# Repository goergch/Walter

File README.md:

# Walter
Walter is a self-made, dangerous, industrial robot with 6 DOF. Right in the middle of development. Check the [Documentation](http://walter.readthedocs.io). Contact me via the [hackaday page](https://hackaday.io/post/53678).

### Contents
    /cad 	    CAD designs (TurboCAD)
    /theory     mainly kinematics
    /code       code of Cortex, Trajectory Planner, and Webserver  
    /schematics schematics of Cortex and its power board
    /docs		source of Walter's [Documentation](https://http://walter.readthedocs.io)
    /datasheets datasheets of components Walter is made of

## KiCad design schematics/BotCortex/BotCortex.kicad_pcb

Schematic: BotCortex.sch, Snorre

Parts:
1.2K1, 1.2K2, 1.2k1, 1.2k2: R; R4
C1: 47uF; C_Radial_D8_L13_P3.8
C2, C6, C12, C14, C16: 100nF; C_Disc_D3_P2.5
C3: 220uF; C_Radial_D5_L6_P2.5
C4, C5: 10uF; C_Radial_D5_L6_P2.5
C7: 47uF; C_Radial_D5_L6_P2.5
C11: 2200uF; C_Radial_D7.5_L11.2_P2.5
C13: 1000uF; C_Radial_D7.5_L11.2_P2.5
D1, D10: Diode; Diode_DO-35_SOD27_Horizontal_RM10
D5: 1N5822; Diode_DO-35_SOD27_Horizontal_RM10
F1: FUSE; FUSE_HOLDER
P1: 2x Serial; Socket_MOLEX-KK-RM2-54mm_Lock_5pin_straight
P2: Herkulex Servo; Molex_KK_6410-04
P3: Encoder Socket 1; Molex_KK_6410-04
P4: Encoder Socket 0; Molex_KK_6410-04
P5: Stepper Elbow; Molex_KK_6410-04
P6: Power In uC Servo 9V; bornier3
P7: Power Out uC Servo; Molex_KK_6410-03
P8: Stepper Forearm; Molex_KK_6410-04
P9: Stepper Wrist; Molex_KK_6410-04
P10: Stepper Upperarm; Molex_KK_6410-04
P11: Stepper Hip; Molex_KK_6410-04
P12: POWER_IN; bornier4
P13: PowerEnableIn; Molex_KK_6410-02
P14: Power Stepper 2; bornier2
P15: Power Stepper 3; bornier2
P16: Power Stepper 4; bornier2
P17: PowerEnableOut; Molex_KK_6410-02
P18: Power Stepper 5; bornier2
P19: Thermal Printer 5V; bornier2
P20: POTI 10K; Molex_KK_6410-03
P21: Reset_Conn; 1pin
P22: Reset Conn; 1pin
P23: LED-Driver-I2C; Molex_KK_6410-04
P24: UART6; PINHEAD1-2
P25: Thermal_Printer; Molex_KK_6410-04
P26: Reset Anschluss; Molex_KK_6410-03
P28: Power Stepper 1; bornier2
Q1, Q2: BC237; TO-92_Molded_Wide
R1: 220; R4
R5, R6: 120; R4
R8, R10: 1K; R4
REL1, REL2: Relay_1xON; RELAIS_HF115F
SW2: reset; SW_PUSH-12mm
U1: 7805; 78XX-TO-220
U2, U3: LM7809ACT; TO-220
U4: Teensy_3.5

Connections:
/3.3V: 1.2K1.1, 1.2K2.1, 1.2k1.1, 1.2k2.1, C16.1, P20.1, P25.4, U4.46 (3.3V_(250mA))
/5V: P12.3, P19.1
/12V: D5.2 (A), P12.2
/24V: F1.1, P12.1
/+5V: C7.1, P3.4, P4.4, P23.1, U1.VO, U4.48 (Vin_(3.3/5V))
/CLK0: P11.2, U4.6 (4/SDA2/PWM)
/CLK1: P10.2, U4.9 (7/SCL0/MOSI0/RX3/PWM)
/CLK2: P8.2, U4.12 (10/TX2/PWM)
/CLK3: P5.2, U4.17 (25)
/CLK4: P9.2, U4.20 (28/MOSI0)
/DIR0: P11.3, U4.7 (5/MISO1/TX1/PWM)
/DIR1: P10.3, U4.10 (8/SDA0/MISO0/TX3/PWM)
/DIR2: P8.3, U4.13 (11/MOSI0)
/DIR3: P5.3, U4.18 (26/SCL2/TX1)
/DIR4: P9.3, U4.21 (29/PWM)
/EN1: P10.4, U4.11 (9/RX2/PWM)
/EN2: P8.4, U4.14 (12/MISO0)
/EN3: P5.4, U4.19 (27/SCK0/RC1)
/EN4: P9.4, U4.22 (30/PWM)
/En0: P11.4, U4.8 (6/PWM)
/LoggerTX: P1.5, U4.24 (32/SCK1/TX4/A13)
/PowerOnServo: P17.2, R10.2
/PowerOnStepper: P17.1, R8.2
/PowerSupplyServo: P13.1, U4.44 (22/A8/PWM)
/PowerSupplyStepper: P13.2, U4.45 (23/A9/PWM)
/RESET: P21.1, P26.2, SW2.2
/RX5: P1.2, U4.26 (34/A15/SDA0/RX5)
/RX6: P24.2, P25.2
/Reset-LED: P26.3, R1.2
/SCl0: 1.2k1.2, P4.3, U4.41 (19/A5/SCL0)
/SCl1: 1.2K2.2, P3.3, P23.3, U4.29 (37/A18/PWM/SCL1)
/SDA0: 1.2k2.2, P4.2, U4.40 (18/A4/SDA0)
/SDA1: 1.2K1.2, P3.2, P23.2, U4.30 (38/A19/PWM/SDA1)
/TX5: P1.3, U4.25 (33/A14SCL0TX5)
/TX6: P24.1, P25.3
/VDDServo9V: P2.2, P6.3
/VDD_Servo_9V: P7.3, REL1.4
/VDD_uC_5V: C1.1, C2.1, C3.1, C6.1, P6.2, P7.2, U1.VI, U2.3 (OUT)
GNDPWR: C1.2, C2.2, C3.2, C6.2, C7.2, C11.2, C12.2, C13.2, C14.2, C16.2, P1.1, P2.1, P3.1, P4.1, P5.1, P6.1, P7.1, P8.1, P9.1, P10.1, P11.1, P12.4, P14.2, P15.2, P16.2, P18.2, P19.2, P20.3, P23.4, P25.1, P26.1, P28.2, Q1.3 (E), Q2.3 (E), SW2.1, U1.GND, U2.2 (GND), U3.2 (GND), U4.1 (GND), U4.34 (GND)
unnamed: C4.2, D10.1 (K), R5.1, REL2.2
unnamed: C5.2, D1.1 (K), R6.1, REL1.2
unnamed: C4.1, C5.1, C11.1, C12.1, D5.1 (K), R5.2, R6.2, U2.1 (IN), U3.1 (IN)
unnamed: C13.1, C14.1, REL1.3, U3.3 (OUT)
unnamed: D1.2 (A), Q1.1 (C), REL1.1
unnamed: D10.2 (A), Q2.1 (C), REL2.1
unnamed: F1.2, REL2.3
unnamed: P2.3, U4.2 (0/MOSI1/RX1)
unnamed: P2.4, U4.3 (1/MISO1/TX1)
unnamed: P14.1, P15.1, P16.1, P18.1, P28.1, REL2.4
unnamed: P20.2, U4.37 (15/A1)
unnamed: P22.1, U4.49 (Reset)
unnamed: Q1.2 (B), R8.1
unnamed: Q2.2 (B), R10.1
unnamed: R1.1, U4.27 (35/A16/PWM)

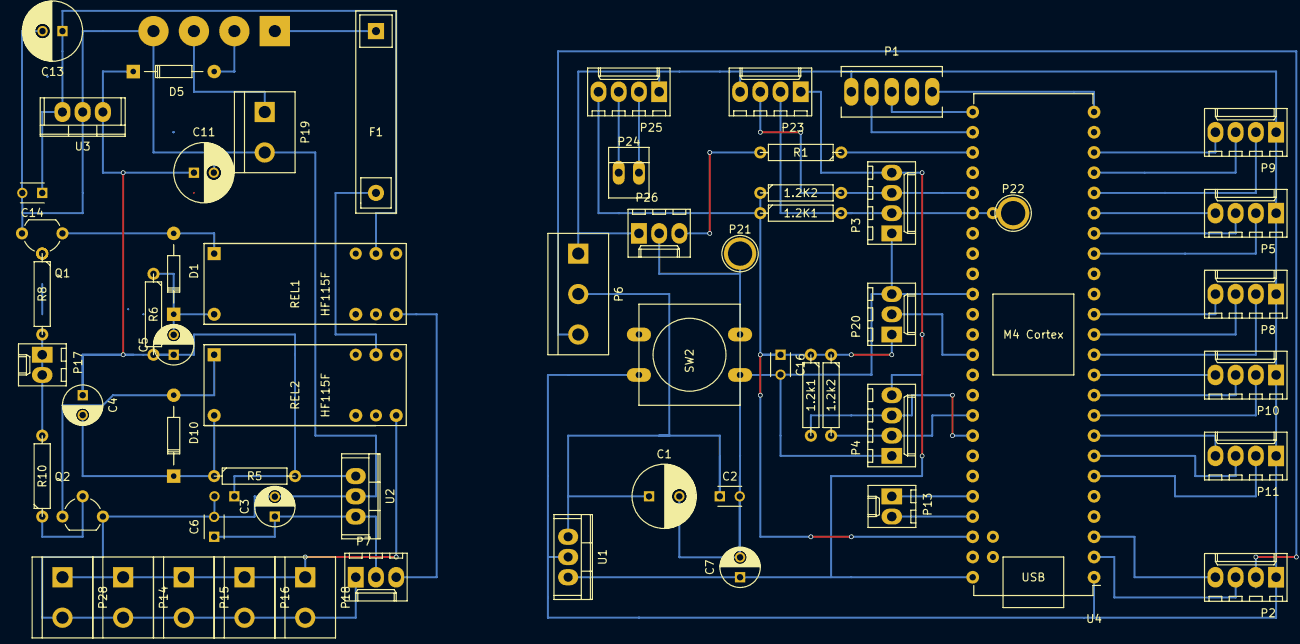
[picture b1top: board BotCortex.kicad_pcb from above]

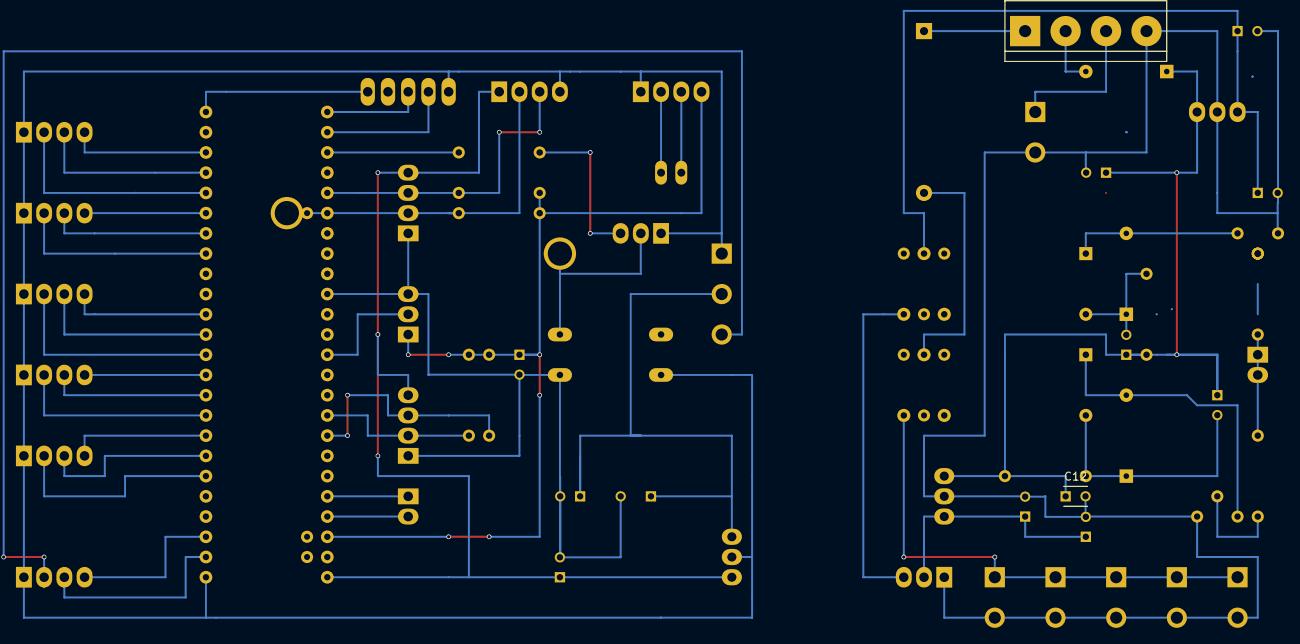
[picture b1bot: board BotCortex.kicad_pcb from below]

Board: 2 copper layers, 61 parts (2 on the bottom side), 54 nets.

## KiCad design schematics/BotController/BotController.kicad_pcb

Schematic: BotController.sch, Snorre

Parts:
AVR1: AVR-ISP-6
C1: 100uF; C_Radial_D8_L13_P3.8
C2, C6, C12, C14, C15, C16: 100nF; C_Disc_D3_P2.5
C3: 220uF; C_Radial_D5_L6_P2.5
C4, C5: 10uF; C_Radial_D5_L6_P2.5
C7: 100uF; C_Radial_D5_L6_P2.5
C11: 2200uF; C_Radial_D7.5_L11.2_P2.5
C13: 1000uF; C_Radial_D7.5_L11.2_P2.5
D1, D10: Diode; Diode_DO-35_SOD27_Horizontal_RM10
D2: LED; LED-3MM
D4: D; Diode_DO-35_SOD27_Horizontal_RM10
D5: 1N5822; Diode_DO-35_SOD27_Horizontal_RM10
F1: FUSE; FUSE_HOLDER
IC1: ATMEGA644A-P; DIP-40_W15.24mm
P1: 2x Serial; Socket_MOLEX-KK-RM2-54mm_Lock_5pin_straight
P2: Herkulex Servo; Molex_KK_6410-04
P3: Encoder Socket 0; Molex_KK_6410-04
P4: Encoder Socket; Molex_KK_6410-04
P5: Stepper 1 WristTurn; Molex_KK_6410-04
P6: Power In uC Servo; bornier3
P7: Power Out uC Servo; Molex_KK_6410-03
P8: Stepper Forearm; Molex_KK_6410-04
P9: Stepper Upperarm; Molex_KK_6410-04
P10: Stepper Shoulder; Molex_KK_6410-04
P11: Stepper Hip; Molex_KK_6410-04
P12: POWER_IN; bornier4
P13: PowerEnableIn; Molex_KK_6410-02
P14: Power Stepper 2; bornier2
P15: Power Stepper 3; bornier2
P16: Power Stepper 4; bornier2
P17: PowerEnableOut; Molex_KK_6410-02
P18: Power Stepper 5; bornier2
P19: ODroid Power; bornier2
P20: POTI 10K; Molex_KK_6410-03
P28: Power Stepper 1; bornier2
Q1, Q2: BC237; TO-92_Molded_Wide
R1: 10K; R4
R2, R8, R10: 1K; R4
R3: 4.7K; R4(8)
R4: 4.7K; R4(7)
R5, R6: 120; R4
REL1, REL2: Relay_1xON; RELAIS_HF115F
SW2: reset; SW_PUSH-12mm
U1: 7805; 78XX-TO-220
U2, U3: LM7809ACT; TO-220
X1: QUARZ_OSSCILATOR; OSC_DIP14

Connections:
/5V: P12.3, P19.1
/12V: D5.2 (A), P12.2
/24V: F1.1, P12.1
/+5V: AVR1.2, C7.1, C16.1, D4.1 (K), IC1.10 (VCC), IC1.30 (AVCC), IC1.32 (AREF), P4.4, P20.1, R1.1, R3.1, R4.1, U1.VO, X1.14
/CLK1: IC1.37 ((PCINT3/ADC3)PA3), P5.2
/CLK2: IC1.34 ((PCINT6/ADC6)PA6), P8.2
/CLK3: IC1.28 ((PCINT22/TOSC1)PC6), P9.2
/CLK4: IC1.25 ((PCINT19/TMS)PC3), P10.2
/CLK5: IC1.20 ((PCINT30/OC2B/ICP)PD6), P11.2
/ConflictEncoderGND: IC1.1 ((PCINT8/T0/XCK)PB0), P3.1
/ConflictEncoderVDD: IC1.2 ((PCINT9/CLKO/T1)PB1), P3.4
/DIR1: IC1.38 ((PCINT2/ADC2)PA2), P5.3
/DIR2: IC1.35 ((PCINT5/ADC5)PA5), P8.3
/DIR3: IC1.29 ((PCINT23/TOSC2)PC7), P9.3
/DIR4: IC1.26 ((PCINT20/TDO)PC4), P10.3
/DIR5: IC1.21 ((PCINT31/OC2A)PD7), P11.3
/EN1: IC1.39 ((PCINT1/ADC1)PA1), P5.4
/EN2: IC1.36 ((PCINT4/ADC4)PA4), P8.4
/EN3: IC1.33 ((PCINT7/ADC7)PA7), P9.4
/EN4: IC1.27 ((PCINT21/TDI)PC5), P10.4
/En5: IC1.24 ((PCINT18/TCK)PC2), P11.4
/LoggerTX: IC1.18 ((PCINT28/XCK1/OC1B)PD4), P1.5
/MISO: AVR1.1, IC1.7 ((PCINT14/MISO)PB6)
/MOSI: AVR1.4, IC1.6 ((PCINT13/MOSI)PB5)
/PowerOnServo: P17.2, R10.2
/PowerOnStepper: P17.1, R8.2
/PowerSupplyServo: IC1.4 ((PCINT11/AIN1/OC0)PB3), P13.1
/PowerSupplyStepper: IC1.5 ((PCINT12/OC0B/~SS~)PB4), P13.2
/RST: AVR1.5, C15.1, D4.2 (A), IC1.9 (~RESET), R1.2, SW2.2
/RXD0: IC1.14 ((PCINT24/RXD0)PD0), P1.2
/RXD1: IC1.16 ((PCINT26/RXD1/INT0)PD2), P2.3
/SCK: AVR1.3, IC1.8 ((PCINT15/SCK)PB7)
/SCl: IC1.22 ((PCINT16/SCL)PC0), P3.3, P4.3, R3.2
/SDA: IC1.23 ((PCINT17/SDA)PC1), P3.2, P4.2, R4.2
/TAL: IC1.13 (XTAL1), X1.8
/TXD0: IC1.15 ((PCINT25/TXD0)PD1), P1.3
/TXD1: IC1.17 ((PCINT27/TXD1/INT1)PD3), P2.4
/VDDServo: P2.2, P6.3
/VDD_Servo: P7.3, REL1.4
/VDD_uC: C3.1, C6.1, P7.2, U2.3 (OUT)
/VDDuC: C1.1, C2.1, P6.2, U1.VI
GNDPWR: AVR1.6, C1.2, C2.2, C3.2, C6.2, C7.2, C11.2, C12.2, C13.2, C14.2, C15.2, C16.2, D2.1 (K), IC1.11 (GND), IC1.31 (GND), P1.1, P1.4, P2.1, P4.1, P5.1, P6.1, P7.1, P8.1, P9.1, P10.1, P11.1, P12.4, P14.2, P15.2, P16.2, P18.2, P19.2, P20.3, P28.2, Q1.3 (E), Q2.3 (E), SW2.1, U1.GND, U2.2 (GND), U3.2 (GND), X1.7
unnamed: C4.2, D10.1 (K), R5.1, REL2.2
unnamed: C5.2, D1.1 (K), R6.1, REL1.2
unnamed: C4.1, C5.1, C11.1, C12.1, D5.1 (K), R5.2, R6.2, U2.1 (IN), U3.1 (IN)
unnamed: C13.1, C14.1, REL1.3, U3.3 (OUT)
unnamed: D1.2 (A), Q1.1 (C), REL1.1
unnamed: D2.2 (A), R2.1
unnamed: D10.2 (A), Q2.1 (C), REL2.1
unnamed: F1.2, REL2.3
unnamed: IC1.3 ((PCINT10/AIN0/INT2)PB2), R2.2
unnamed: IC1.40 ((PCINT0/ADC0)PA0), P20.2
unnamed: P14.1, P15.1, P16.1, P18.1, P28.1, REL2.4
unnamed: Q1.2 (B), R8.1
unnamed: Q2.2 (B), R10.1

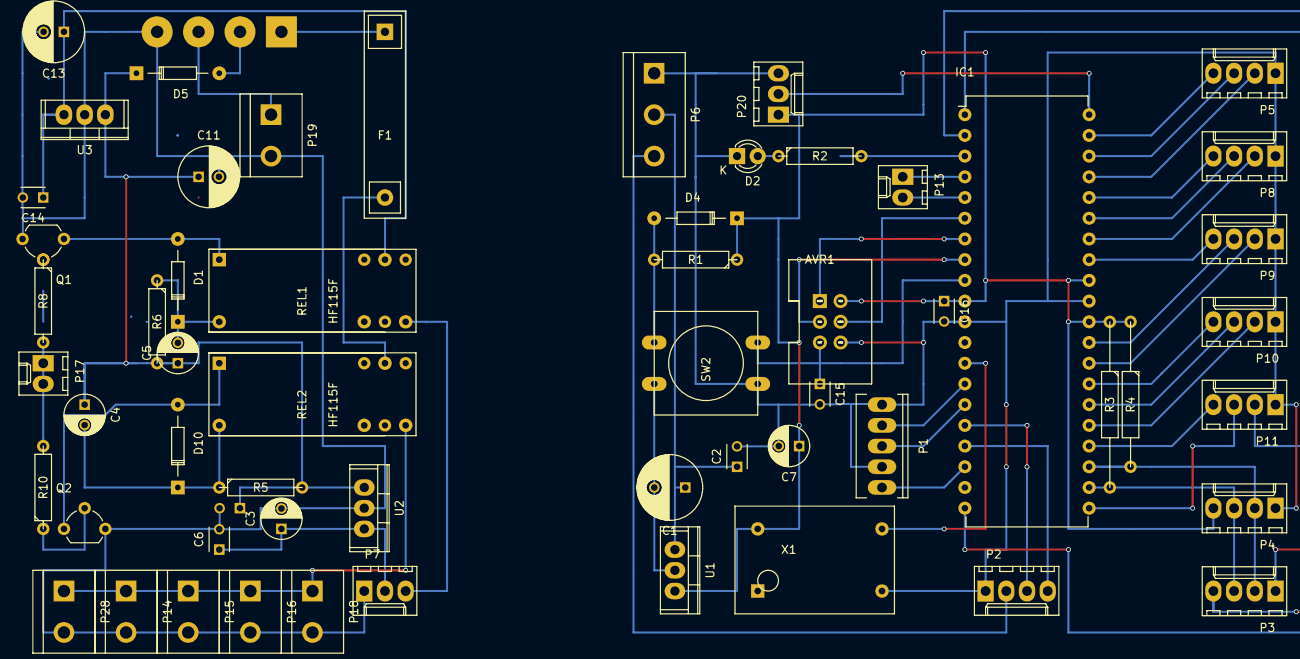
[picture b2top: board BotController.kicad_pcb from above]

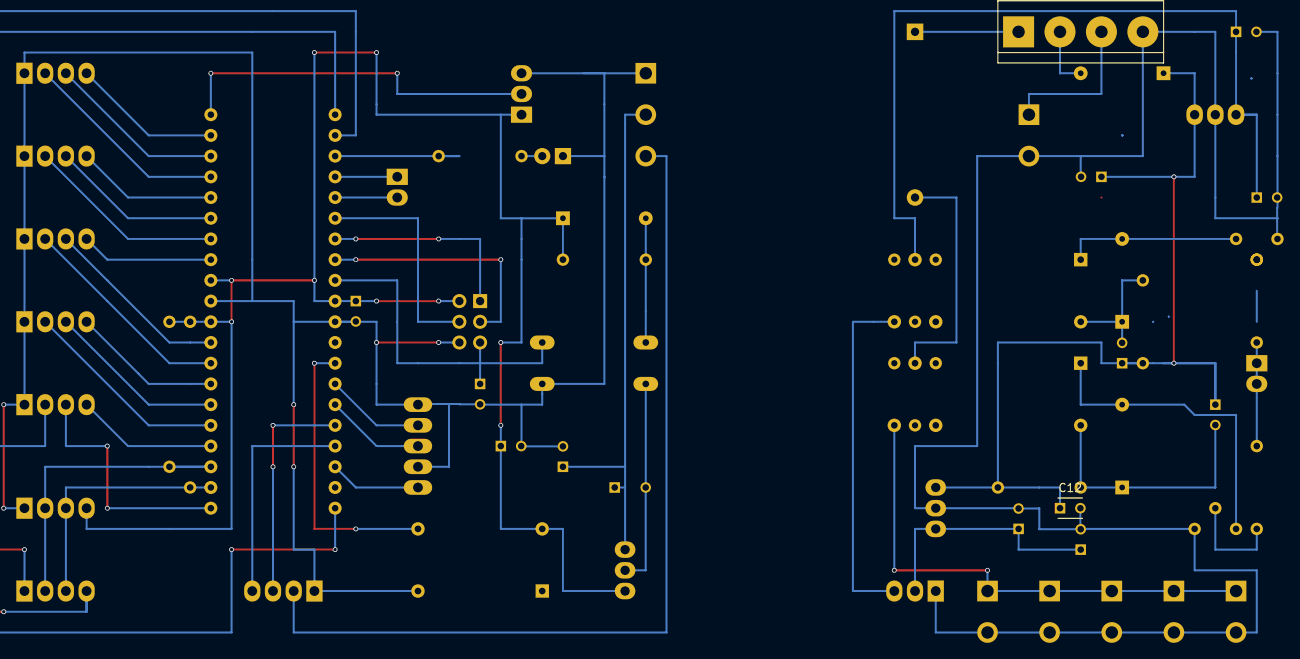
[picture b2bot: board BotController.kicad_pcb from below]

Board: 2 copper layers, 59 parts (2 on the bottom side), 55 nets.

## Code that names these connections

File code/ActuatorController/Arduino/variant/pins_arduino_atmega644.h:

/*
  pins_arduino.h - Pin definition functions for Arduino
  Part of Arduino - http://www.arduino.cc/

  Copyright (c) 2007 David A. Mellis

  This library is free software; you can redistribute it and/or
  modify it under the terms of the GNU Lesser General Public
  License as published by the Free Software Foundation; either
  version 2.1 of the License, or (at your option) any later version.

  This library is distributed in the hope that it will be useful,
  but WITHOUT ANY WARRANTY; without even the implied warranty of
  MERCHANTABILITY or FITNESS FOR A PARTICULAR PURPOSE.  See the GNU
  Lesser General Public License for more details.

  You should have received a copy of the GNU Lesser General
  Public License along with this library; if not, write to the
  Free Software Foundation, Inc., 59 Temple Place, Suite 330,
  Boston, MA  02111-1307  USA

  $Id: wiring.h 249 2007-02-03 16:52:51Z mellis $
*/

#ifndef Pins_Arduino_AtMega644_h
#define Pins_Arduino_AtMega644_h

#include <avr/pgmspace.h>

#define NUM_DIGITAL_PINS			32
#define NUM_ANALOG_INPUTS           8

#define analogInputToDigitalPin(p)  ((p < 6) ? (p) + 14 : -1)

// PWM pins are  PD4, PD5, PD6, PD7, PB3, PB4,
#define digitalPinHasPWM(p)         ((p) == 4 || (p) == 5 || (p) == 6 || (p) == 7 || (p) == 11 || (p) == 12))

static const uint8_t SS   = 12;
static const uint8_t MOSI = 13;
static const uint8_t MISO = 20;
static const uint8_t SCK  = 21;


static const uint8_t SDA = 15;
static const uint8_t SCL = 14;

static const uint8_t PIN_D0 = 0;
static const uint8_t PIN_D1 = 1;
static const uint8_t PIN_D2 = 2;
static const uint8_t PIN_D3 = 3;
static const uint8_t PIN_D4 = 4;
static const uint8_t PIN_D5 = 5;
static const uint8_t PIN_D6 = 6;
static const uint8_t PIN_D7 = 7;

static const uint8_t PIN_B0 = 8;
static const uint8_t PIN_B1 = 9;
static const uint8_t PIN_B2 = 10;
static const uint8_t PIN_B3 = 11;
static const uint8_t PIN_B4 = 12;
static const uint8_t PIN_B5 = 13;

static const uint8_t PIN_C0 = 14;
static const uint8_t PIN_C1 = 15;
static const uint8_t PIN_C2 = 16;
static const uint8_t PIN_C3 = 17;
static const uint8_t PIN_C4 = 18;
static const uint8_t PIN_C5 = 19;

static const uint8_t PIN_B6 = 20;
static const uint8_t PIN_B7 = 21;
static const uint8_t PIN_C6 = 22;
static const uint8_t PIN_C7 = 23;

static const uint8_t PIN_A0 = 24;
static const uint8_t PIN_A1 = 25;
static const uint8_t PIN_A2 = 26;
static const uint8_t PIN_A3 = 27;
static const uint8_t PIN_A4 = 28;
static const uint8_t PIN_A5 = 29;
static const uint8_t PIN_A6 = 30;
static const uint8_t PIN_A7 = 31;

/*
static const uint8_t A0 = 24;
static const uint8_t A1 = 25;
static const uint8_t A2 = 26;
static const uint8_t A3 = 27;
static const uint8_t A4 = 28;
static const uint8_t A5 = 29;
static const uint8_t A6 = 30;
static const uint8_t A7 = 31;
*/

#define digitalPinToPCICR(p)    (((p) >= 0 && (p) <= 21) ? (&PCICR) : ((uint8_t *)0))
#define digitalPinToPCICRbit(p) (((p) <= PIN_D7) ? 3 : ((((p) <= PIN_B5)) ? 1 : (((p) <= PIN_C5)?2:(((p) <= PIN_B7)? 1:2))))
// #define digitalPinToPCMSK(p)    (((p) <= 7) ? (&PCMSK3) : (((p) <= 13) ? (&PCMSK1) : (((p) <= 21) ? (&PCMSK1) : ((uint8_t *)0))))
// #define digitalPinToPCMSKbit(p) (((p) <= 7) ? (p) : (((p) <= 13) ? ((p) - 8) : ((p) - 14)))

#define digitalPinToPCMSK(p)    ( ((p) <= PIN_D7) ? (&PCMSK3) : (((p) <= PIN_B5) ? (&PCMSK1) : (((p) <= PIN_C5) ? (&PCMSK2) : ((p) <= PIN_B7) ? (&PCMSK1) :  ((p) <= PIN_C7) ? (&PCMSK2) : (&PCMSK0))))
#define digitalPinToPCMSKbit(p) ( ((p) <= PIN_D7) ? (p) :       (((p) <= PIN_B5) ? ((p) - 8) : (((p) <= PIN_C5) ? ((p)-14) :  ((p) <= PIN_B7) ? ((p)-20+6) : ((p) <= PIN_C7) ? ((p)-22+6) :((p)-24))))


#ifdef ARDUINO_MAIN

// On the Arduino board, digital pins are also used
// for the analog output (software PWM).  Analog input
// pins are a separate set.

// ATMEL ATMEGA644 
//
//                   +--\/--+
//       XCK0/T0 PB0  1|      |40  PA0 ADC0  
//       CLK0/T1 PB1  2|      |39  PA1 ADC1  
//     INT2/AIN0 PB2  3|      |38  PA2 ADC2   
//     OC0A/AIN1 PB3  4|      |37  PA3 ADC3   
//       OC0B/SS PB4  5|      |36  PA4 ADC4   
//          MOSI PB5  6|      |35  PA5 ADC5  
//          MISO PB6  7|      |34  PA6 ADC6
//           SCK PB7  8|      |33  PA7 ADC7
//             RESET  9|      |32  AVCC
//               VCC 10|      |31  GND       
//               GND 11|      |30  AVCC       
//             XTAL2 12|      |29  PC7 TOSC2     
//             XTAL1 13|      |28  PC6 TOSC1     
//           RXD PD0 14|      |27  PC5 TDI      
//         T  XD PD1 15|      |26  PC4 TDO      
//          INT0 PD2 16|      |25  PC3 TMS       
//          INT1 PD3 17|      |24  PC2 TCK      
//          OC1B PD4 18|      |23  PC1 SDA      
//          OC1A PD5 19|      |22  PC0 SCL      
//     OC2B/ICP1 PD6 20|      |21  PD7 OC2A     
//                     +------+    
// ATMEL ATMEGA1280 / ARDUINO
//
// 0-7 PE0-PE7   works
// 8-13 PB0-PB5  works
// 14-21 PA0-PA7 works 
// 22-29 PH0-PH7 works
// 30-35 PG5-PG0 works
// 36-43 PC7-PC0 works
// 44-51 PJ7-PJ0 works
// 52-59 PL7-PL0 works
// 60-67 PD7-PD0 works
// A0-A7 PF0-PF7
// A8-A15 PK0-PK7


// these arrays map port names (e.g. port B) to the
// appropriate addresses for various functions (e.g. reading
// and writing)
const uint16_t PROGMEM port_to_mode_PGM[] = {
	NOT_A_PORT,
	(uint16_t) &DDRA,
	(uint16_t) &DDRB,
	(uint16_t) &DDRC,
	(uint16_t) &DDRD,
};

const uint16_t PROGMEM port_to_output_PGM[] = {
	NOT_A_PORT,
	(uint16_t) &PORTA,
	(uint16_t) &PORTB,
	(uint16_t) &PORTC,
	(uint16_t) &PORTD,
};

const uint16_t PROGMEM port_to_input_PGM[] = {
	NOT_A_PORT,
	(uint16_t) &PINA,
	(uint16_t) &PINB,
	(uint16_t) &PINC,
	(uint16_t) &PIND,
};

const uint8_t PROGMEM digital_pin_to_port_PGM[] = {
	PD, /* 0 */
	PD,
	PD,
	PD,
	PD,
	PD,
	PD,
	PD,
	PB, /* 8 */
	PB,
	PB,
	PB,
	PB,
	PB,
	PC, /* 14 */
	PC,
	PC,
	PC,
	PC,
	PC,
	PB, /* 20 */
	PB,
	PC,
	PC,
	PA, /* 24 */
	PA, 
	PA, 
	PA, 
	PA, 
	PA, 
	PA, 
	PA, /*  31 */
};

const uint8_t PROGMEM digital_pin_to_bit_mask_PGM[] = {
	_BV(0), /* 0, port D */
	_BV(1),
	_BV(2),
	_BV(3),
	_BV(4),
	_BV(5),
	_BV(6),
	_BV(7),
	_BV(0), /* 8, port B */
	_BV(1),
	_BV(2),
	_BV(3),
	_BV(4),
	_BV(5),
	_BV(0), /* 14, port C */
	_BV(1),
	_BV(2),
	_BV(3),
	_BV(4),
	_BV(5),
	_BV(6), /* 20, port B */
	_BV(7),
	_BV(6), /* 22, port C */
	_BV(7),
	_BV(0), /* 24, port A */
	_BV(1), 
	_BV(2), 
	_BV(3), 
	_BV(4), 
	_BV(5), 
	_BV(6), 
	_BV(7), /* 31*/
};

const uint8_t PROGMEM digital_pin_to_timer_PGM[] = {
	NOT_ON_TIMER,       // PD0 /* 0 - port D */
	NOT_ON_TIMER,		// PD1
	NOT_ON_TIMER,		// PD2
	NOT_ON_TIMER,		// PD3
	TIMER1B,			// PD4
	TIMER1A,			// PD5
	TIMER2B,			// PD6
	TIMER2A,			// PD7
	NOT_ON_TIMER,		// PB0 /* 8 - port B */
	NOT_ON_TIMER,		// PB1
	NOT_ON_TIMER,		// PB2
	TIMER0A,			// PB3
	TIMER0B,			// PB4
	NOT_ON_TIMER,		// PB5
	NOT_ON_TIMER,		// PB6
	NOT_ON_TIMER,		// PC0 /* 14 - port C */
	NOT_ON_TIMER,		// PC1 
	NOT_ON_TIMER,		// PC2 
	NOT_ON_TIMER,		// PC3 
	NOT_ON_TIMER,		// PC4 
	NOT_ON_TIMER,		// PC5 
	NOT_ON_TIMER,		// PB6 /* 20 - port B */
	NOT_ON_TIMER,		// PB7 
	NOT_ON_TIMER,		// PC6 /* 22 - port C */
	NOT_ON_TIMER,		// PA0 
	NOT_ON_TIMER,		// PA1 /* 24 - port A */
	NOT_ON_TIMER,		// PA1
	NOT_ON_TIMER,		// PA2 
	NOT_ON_TIMER,		// PA3 
	NOT_ON_TIMER,		// PA4 
	NOT_ON_TIMER,		// PA5 
	NOT_ON_TIMER,		// PA6 
	NOT_ON_TIMER,		// PA7 
	NOT_ON_TIMER,		// PA8 /* 31 */
};

#endif // ifdef ARDUINO_MAIN

#endif // Ifdef Pins_Arduino_h

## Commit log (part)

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2017-01-27 modified serialization
2017-01-27 new images
2017-01-27 eclipse project WalterPlanner re-setup
2017-01-27 Housing CAD'ed
2017-01-28 added Reset LED to schematics and Cortex
2017-01-28 socket for bot cable amended
2017-01-29 changed LED pattern during start up
2017-01-29 rebuild workspace
2017-01-29 Bugfix: power /enable/setup LEDs were not displayed during setup phase
2017-01-29 added commens
2017-01-30 updated doc
2017-01-30 images
2017-01-30 wiki
2017-02-01 no message
2017-02-01 Set theme jekyll-theme-minimal
2017-02-01 Set theme jekyll-theme-slate
2017-02-01 Create CNAME
2017-02-01 Set theme jekyll-theme-cayman
2017-02-01 setup wiki
2017-02-01 gallery
2017-02-02 wrist documentation
2017-02-02 doc wrist
2017-02-02 moved images
2017-02-03 Bugfix: Post request with Poco requires "content-length" of body
2017-02-03 shortened setup time
2017-02-03 typo
2017-02-03 made walls of housing bigger (1.5mm -> 2mm)
2017-02-04 wrong path fixed
2017-02-04 typos
2017-02-04 i2c pullup resistor reduced to 1.1K since i2c lines capacity was 400pF
2017-02-04 improved I2C bus
2017-02-04 Bugfix in Adafruits Library for Tiny Thermal Printer: UpsideDown sent wrong esc sequence
2017-02-04 reduced delay
2017-02-04 new command println
2017-02-04 integrated new command println and added printer datasheet
2017-02-05 bugfix: mongoose.h must be first include. Otherwise strange SEGV happen
2017-02-05 wiki upperarm
2017-02-05 upperarm wiki
2017-02-05 Weekend
2017-02-06 moved doc
2017-02-08 moved files around
2017-02-09 Set theme jekyll-theme-dinky
2017-02-09 new feature: trajectory can stop between each pieces via new button
2017-02-09 new feature: trajectory nodes without a name are given a number
2017-02-09 new picture
2017-02-09 wiki page about planner ui
2017-02-09 nicer picture for wiki
2017-02-10 add code comments
2017-02-10 video on WalterPlanner
2017-02-10 reorganized cad files
2017-02-10 animated gif
2017-02-10 readme with animated gif
2017-02-10 videos for wiki
2017-02-11 cortex socket was too tight
2017-02-12 Bugfix: If lIghtscontroller not connected cortex was stuck
2017-02-12 updated github pages
2017-02-12 intro was doubled
2017-02-12 picture of myself
2017-02-12 reduced pullup resistors in I2C lines
2017-02-12 changed "Walter"-plate
2017-02-12 cleanup
2017-02-12 stl files for planning UI
2017-02-15 wiki refactored
2017-02-17 Implementation of Towers of Hanoi started
2017-02-17 Introduced Gripper distance instead of angle
2017-02-17 basics of towers of hanoi done
2017-02-18 implemented raw read from sensor
2017-02-18 replaced delayMicrosoconds by delay with yield
2017-02-18 corrected bug in visualization of gripper
2017-02-18 adapted timing of hanoi trajectory
2017-02-18 better timing
2017-02-18 corrected null positions
2017-02-18 improved sample rate for Herkulex
2017-02-18 small things
2017-02-18 Bug: when encoder was down, stepper turned in wrong direction
2017-02-18 corrected wrong dimensions of gripper
2017-02-18 inmproved grip force without overloading servo
2017-02-18 removed old stuff
2017-02-18 Console panel has a frame like Walter-plate
2017-02-18 kabelloch im stecker vergößert, abgeschirmtes Kabel ist dicker
2017-02-18 Towers of Hanoi now consider disk diameter
2017-02-18 socket
2017-02-19 renamed
2017-02-19 herkulex torque detection improvement
2017-02-19 new pictures
2017-02-19 pictures
2017-02-19 wiki housing
2017-02-19 wiki drawing of cabinet
2017-02-19 wiki pictures
2017-02-19 core refactored
2017-02-20 added comments
2017-02-20 refactored
2017-02-25 new cortex command "setup force" to leave power on even if errors occur
2017-02-25 renamed some variables
2017-02-26 spaces
2017-02-26 removed old images
2017-03-11 Towers of Hanoi work now and some bugfixes
2017-03-11 dwg for Ben
2017-03-11 Serious Bug in Kinematics: wrong sign in angle4, strange enough the downstream selection of solutions compensated that
2017-03-12 reduced acceleration of upper arm due to resonances
2017-03-12 Default webserver runs on Odroid now
2017-03-12 slightly adapted dimensions
2017-03-12 introduced default tcp deviation
2017-03-12 movements improved
2017-03-12 reduced max pose acceleration even more
2017-03-12 bug in kinematic found
2017-03-12 beautified
2017-03-13 wrong sign
2017-03-15 movement speed up
2017-03-23 added freeglut library for windows
2017-04-10 more or less final
